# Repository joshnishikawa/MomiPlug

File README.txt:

TEENSY 3.1 PIN ASSIGNMENTS
             ______
        ____|      |____
  GND -|-GND|      | 5V |- VBUS on USB host module
 MIDI -| 0  |______AGND-|- AGND (sleve and Mux16 GND)
 FS 1 -| 1        _3.3v-|- Voltage
SEL_A  |-2   AREF(_) 23 |- 1/4" analog return (ring)
SEL_B  |-3    A-1(_) 22-|  SER (display)
SEL_C  |-4    A-2(_) 21-|  Encoder Pin B
SEL_D  |-5           20-|  Encoder Pin A
 FS 0  |-6           19-| 'Edit' Button
 SRCK -| 7           18 |- Button 4
 RCLK -| 8           17 |- Button 3
  INT -| 9           16 |- Button 2
   SS  |-10          15 |- Button 1
 MOSI  |-11          14 |- Button 0
 MISO  |-12          13 |- SCK
       |________________|

  * '-' indicates which direction the wires run.

74HC595 (x2) PIN ASSIGNMENTS
             __ __
 Butn4 LED -| (_) |- 5V
 Butn3 LED -|     |- Butn5 LED
 Butn2 LED -|     |- SER from Teensy
 G Segment -|     |-
 F Segment -|  #1 |- RCLK
 E Segment -|     |- SRCK
 D Segment -|     |- 5V
       GND -|_____|- SER to #2
             __ __
 B Segment -| (_) |- 5V
 A Segment -|     |- C Segment
DP Segment -|     |- SER from #1
 Cathode 1 -|     |-
 Cathode 2 -|  #2 |- RCLK
 Cathode 3 -|     |- SRCK
 Butn1 LED -|     |- 5V
       GND -|_____|-

 * The 7 segments are split between
   the 2 chips so that a maximum of
   5 pins are HIGH at any given time.

7-SEGMENT LED PIN ASSIGNMENTS

      G  F  DP A  B
 _____|__|__|__|__|_
|O ___ O ___ O ___  |
| |   | |   | |   | |
| |___| |___| |___| |
| |   | |   | |   | |
| |___| |___| |___| |
|___________________|
   |  |  |  |  |  |
   E  1  2  C  D  3

 *It's wired up-side down so
  ignore the datasheet.

USB HOST MODULE PIN ASSIGNMENTS (from circuits@home)
          __________
         |          |
         |          |
       __|          |__
      |  |          |  |
      |  |__________|  |
      | _    5V -(_) _ |- (Be sure to break the VBUS jumper.)
  SS -|(_)          (_)|
MOSI -|(_)          (_)|
MISO -|(_)          (_)|
 SCK -|(_)          (_)|
      |(_)          (_)|
      |(_)          (_)|
      |(_)          (_)|
      |(_)          (_)|
3.3V -|(_)          (_)|- GND
      |(_)          (_)|- 3.3V
 GND -|(_)          (_)|
      |(_)          (_)|
      |________________|

5-PIN MIDI IN DIN PIN ASSIGNMENTS
_______________________
                       \
________________________\
      _____________      |
     /_____________\     |     ______________
    //      _2     \\    |    /     2    \   \__
   // 4_   (_)   _5 \\   |   / 5   0===  4\   \ \___
  ||  (_)       (_)  ||  |  |  0===     0==|        \
  ||  _           _  ||  |  |              |         |__
  || (_)         (_) ||  |  | 0===       0=|         |_ \
  || 1             3 ||  |  | 3          1 |         | \ \
  ||                 ||  |  |              |     ___/   \ \
   \\       _       //   |   \      _     /   /_/       / /
    \\_____| |_____//    |    \____| |___/___/         / /
     \-------------/     |                            / / 
_________________________|                            \ \

Pin 1 - Not Connected
Pin 2 - Not Connected
Pin 3 - Not Connected
Pin 4 - Through a 220 Ohm resistor and into 6N138 Pin 2
Pin 5 - From 6N138 Pin 3 

 * A diode and 270 Ohm resistor are also needed.
   See schematic below.

MIDI IN SCHEMATIC (6N138)        3.3V
                                  |
                           __ __  |   270 Ohm
            220 Ohm      -|1(_)8|~'~~~\/\/\/\_
DIN Pin 4~~~\/\/\/\~~~_~~~|2   7|-            |
DIN Pin 5~~~~~~~~~~~~~^~~~|3   6|~~~~~~~~~~~~~'~~~MIDI
                      D  -|4___5|~~GND          (Teensy)
                      i
                      o
                      d
                      e

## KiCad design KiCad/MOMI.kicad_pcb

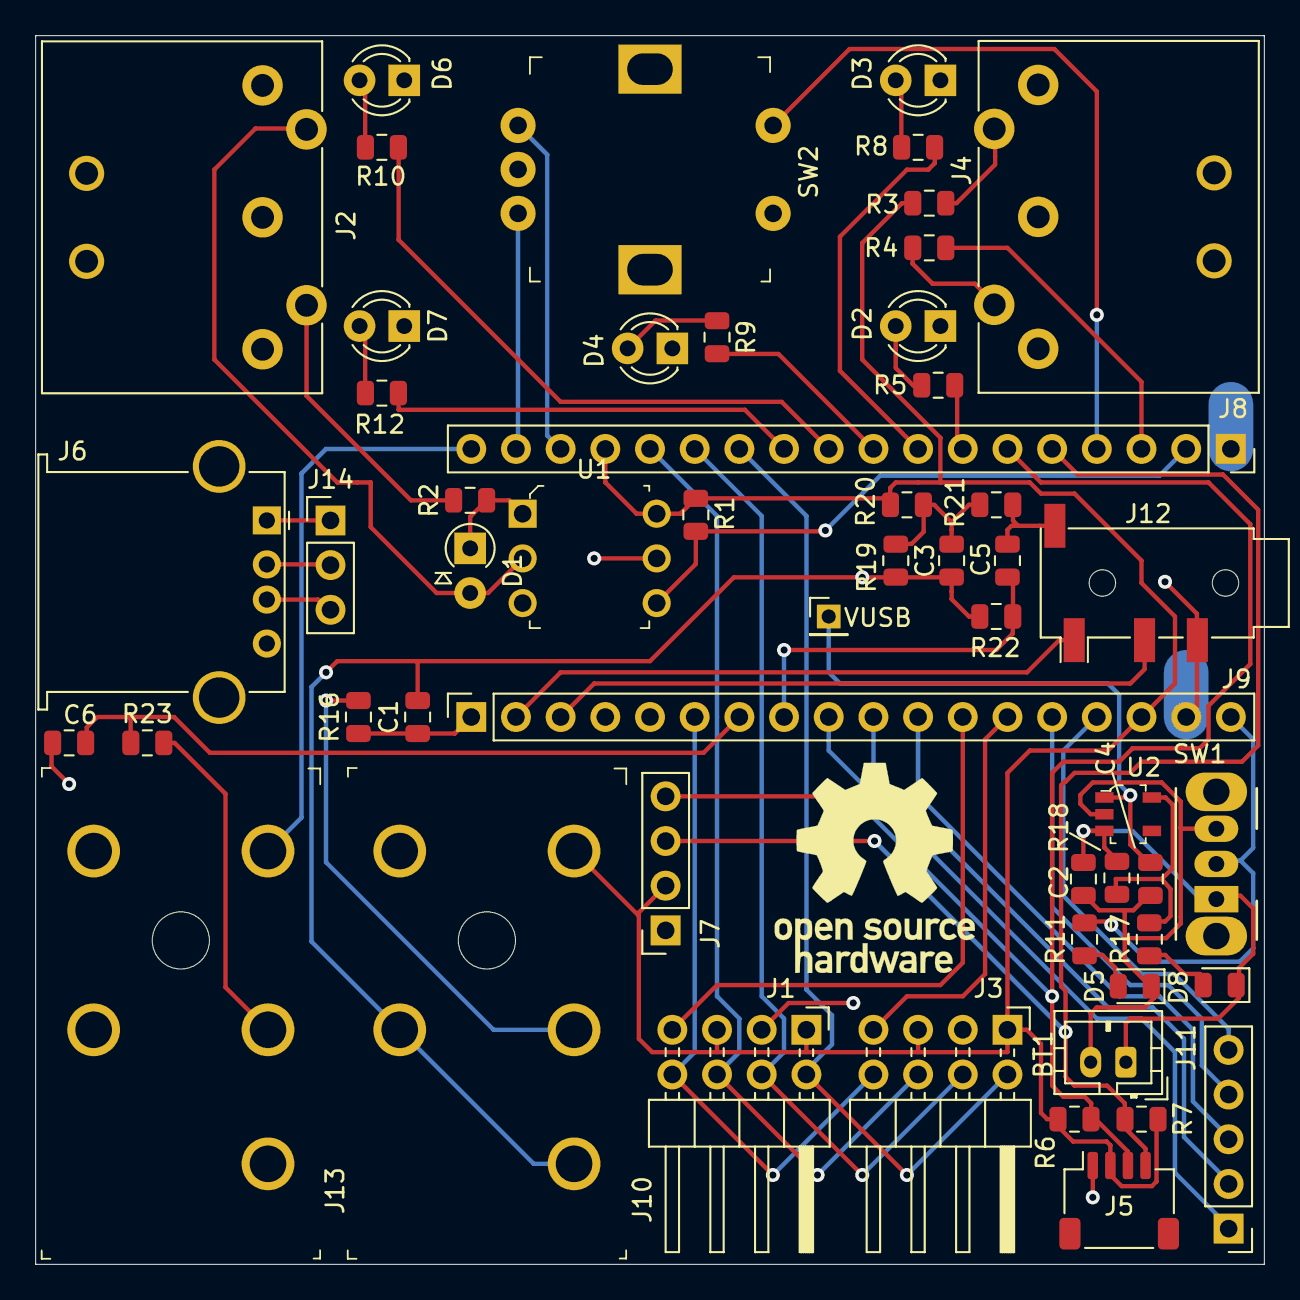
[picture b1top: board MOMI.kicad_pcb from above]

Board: 2 copper layers, 69.8 x 69.8 mm, 53 parts (0 on the bottom side), 55 nets.

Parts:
BT1: Battery_Cell; JST_PH_B2B-PH-K_1x02_P2.00mm_Vertical
C1, C3, C5, C6: 10uF; C_0805_2012Metric
C2, C4: 1uF; C_0805_2012Metric
D1: D; D_A-405_P2.54mm_Vertical_AnodeUp
D2: Green LED; LED_D3.0mm
D3, D4, D6: Red LED; LED_D3.0mm
D5: Green LED; LED_0805_2012Metric
D7: Blue LED; LED_D3.0mm
D8: Red LED; LED_0805_2012Metric
J1, J3: Conn_02x04_Male; PinHeader_2x04_P2.54mm_Horizontal
J2: MIDI in; SDS-50J
J4: MIDI out; SDS-50J
J5: JST 1mm (I2C); JST_SH_SM04B-SRSS-TB_1x04-1MP_P1.00mm_Horizontal
J6: USB_A; USB_A_Stewart_SS-52100-001_Horizontal
J7: Conn_01x04_Female; PinSocket_1x04_P2.54mm_Vertical
J8, J9: Conn_01x18_Female; PinSocket_1x18_P2.54mm_Vertical
J10: Expression Pedal; Headphone_Jack_6.35mm_RA49B14B
J11: Conn_01x05_Male; PinHeader_1x05_P2.54mm_Vertical
J12: AudioJack4; Jack_3.5mm_PJ320D_Horizontal
J13: Dual Footswitch; Headphone_Jack_6.35mm_RA49B14B
J14: Conn_01x03_Male; Pin_Header_Straight_1x03_Pitch2.54mm
R1: 270; R_0805_2012Metric
R2, R3, R4: 220; R_0805_2012Metric
R5, R8, R9, R10, R11, R12, R17: 330; R_0805_2012Metric
R6, R7: 4.7k; R_0805_2012Metric
R16, R21, R22, R23: 47k; R_0805_2012Metric
R18: 100k; R_0805_2012Metric
R19: 2.2k; R_0805_2012Metric
R20: 10k; R_0805_2012Metric
SW1: SW_SPDT; SW_CuK_OS102011MA1QN1_SPDT_Angled
SW2: Encoder_Switch; Rotary_Encoder_Switched_PEC11R
U1: H11L1M; DIP-6_W7.62mm
U2: MAX1555EZK_T; SOT-753

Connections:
3.3V: J1.1, J1.5, J3.1, J3.5, J5.2, J7.2, J8.15, J9.16, J10.T, R1.2, R3.1, R6.2, R7.1, R20.1, U1.6
AGND: C1.2, C3.2, J9.17, J10.RN, J10.S, J12.R2, R19.1, R22.1
GND: BT1.2, C2.2, C4.2, C6.2, D2.1, D3.1, D4.1, D5.1, D6.1, D7.1, J1.3, J3.3, J4.2, J5.1, J6.4, J6.5, J7.1, J8.1, J9.4, J13.S, SW1.3, SW2.C, SW2.S2, U1.5, U2.2
unnamed: BT1.1, C2.1, D8.1, R18.2, SW1.1, U2.3
unnamed: C1.1, J9.1, R16.1
unnamed: C3.1, R19.2, R20.2, R21.1
unnamed: C5.1, J12.S, R21.2
unnamed: C5.2, J9.8, R22.2
unnamed: C6.1, J9.7, R23.1
unnamed: D1.1, R2.2, U1.1
unnamed: D1.2, J2.5, U1.2
unnamed: D2.2, R5.1
unnamed: D3.2, R8.1
unnamed: D4.2, R9.1
unnamed: D5.2, R11.1
unnamed: D6.2, R10.1
unnamed: D7.2, R12.1
unnamed: D8.2, R17.1
unnamed: J2.4, R2.1
unnamed: J4.4, R3.2
unnamed: J4.5, R4.2
unnamed: J8.2, R1.1, U1.4
unnamed: J8.3, R4.1
unnamed: J8.4, SW2.S1
unnamed: J8.7, R5.2
unnamed: J8.8, R8.2
unnamed: J8.9, R9.2
unnamed: J8.10, R10.2
unnamed: J8.11, R12.2
unnamed: J8.16, SW2.A
unnamed: J8.17, SW2.B
unnamed: J9.18, R11.2, SW1.2
unnamed: J10.R, R16.2
unnamed: J9.9, J11.1
unnamed: J9.10, J11.2
unnamed: J9.11, J11.3
unnamed: J9.14, J11.4
unnamed: J9.15, J11.5
unnamed: J9.3, J12.R1
unnamed: J9.2, J12.T
unnamed: J13.R, R23.2
unnamed: J8.18, J13.T
unnamed: J6.1, J14.1
unnamed: J6.2, J14.2
unnamed: J6.3, J14.3
unnamed: R17.2, R18.1, U2.5
SCL: J5.4, J7.3, J8.5, R7.2
SDA: J5.3, J7.4, J8.6, R6.1
SEL0: J1.2, J3.2, J8.12
SEL1&MOSI0: J1.4, J3.4, J8.13
SEL2&MISO0: J1.6, J3.6, J8.14
SEL3&SCK0: J1.8, J3.8, J9.6
SIG0&CSO: J1.7, J9.12
SIG1&CSO: J3.7, J9.13
VUSB: C4.1, U2.1

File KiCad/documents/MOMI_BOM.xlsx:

Comment | Designator | Footprint | LCSC Part #（optional）
10uF | C1,C3,C5,C6 | C_0805_2012Metric
1uF | C2,C4 | C_0805_2012Metric
Green LED | D5 | LED_0805_2012Metric
Red LED | D8 | LED_0805_2012Metric
270 | R1 | R_0805_2012Metric
220 | R2,R3,R4 | R_0805_2012Metric
330 | R5,R8,R9,R10,R12,R11,R17 | R_0805_2012Metric
4.7k | R6,R7 | R_0805_2012Metric
10k | R13,R14,R15,R20 | R_0805_2012Metric
47k | R16,R21,R22,R23 | R_0805_2012Metric
2.2k | R19 | R_0805_2012Metric
100k | R18 | R_0805_2012Metric

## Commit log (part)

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2015-04-30 :confetti_ball: Added .gitattributes & .gitignore files
2015-11-23 Updated to work with MIDIcontroller 2.0
2015-11-23 Made CC the default mode (not track)
2016-01-04 Improved display
    Display now uses bitwise logic and shiftOut() for better portability
    with MUCH less code.
2016-01-09 MIDI to usbMIDI thru
2016-05-16 Preparing for Onboard Editing Capability
    The editor class now detects user triggered input and calls the
    appropriate function for the input type (although the function doesn't
    do anything yet). A new? 'track' class handles arm, record and volume
    for DAW tracks.
2016-05-23 now using EEPROM
    EEPROM now stores button, footswitch and track states, track and encoder
    levels. Changed some data types and sorted public and private variables.
    Buttons now display CC number when ON; 0 when OFF. Used longer bounce
    time. editChannel() only requires one argument. edit() still doesn't
    work.
2016-05-26 EDITOR MATERIALIZES!!!
    The Editor now changes numbers, min, max and modes for buttons or pots
    and saves values to EEPROM. Editor now acts as a MIDI encoder. Display
    supports more characters and now blinks a DP. Added more keywords.
2016-05-26 Fully working sketch
    Numerous updates and sweeping changes. The sketch is now fully
    functional but a lot of it probably could be bounced out to functions or
    even other files.
2016-05-27 Pause MUX read
    New variable allows user to change their mind about which control to
    edit before the edit button is released.
2016-06-12 MIDI in chaos()
    Overloaded states() function which allows blink() to be called for DP by
    ignoring them. chaos() is now for MIDI input.
2016-09-21 MIDI input cleanup
    I still wouldn't call it clean though.
2018-05-13 cleanup
2018-06-19 Consolidated the entire MOMIPLUG project
    Consolidated everything related to MOMIPLUG into one project.
2019-09-30 Everything works ;^)
    *Added option to calibrate Touch sensor.
    *MIDI out now works.
    *Use 2 MIDI out ports and 2 usbMIDI out ports.
    *sel_b changed to a pin that's not dead
    *Keep certain MIDI controllers active in "track" mode
2019-10-03 Mouved callbacks out of main sketch
2019-11-14 Improved Touch Support
    Now uses objects from the updated Flicker library. Exterminated all bools. chaos() uses elapsedMillis to keep time.
2019-11-14 Archived Older Versions
2019-11-14 Folder Tree Change
2019-11-20 Various Improvements
    editor.target and editor.editme are now one variable (but should be a group of bools...later, eh?)
    Fixed a bug where the MIDI channel was being set to 255.
    Threshold for onboard buttons is auto-detected.
2019-11-24 New Features
    Added USBhost input to the chaos() function. Made chaos() more chaotic. Added a 2 second timer on the enable pins so you can safely hotplug (but not hot-unplug foot controllers). Now, in edit mode, a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
2019-11-25 Bugfix (again)
2019-11-28 Minor improvements
2020-01-17 Added KiCad files
2020-04-23 Add KiCad files
2021-11-21 new pinout for circuit board
2022-10-15 removed images
2023-01-21 1/21/2023
2023-03-26 MOMI3 init
